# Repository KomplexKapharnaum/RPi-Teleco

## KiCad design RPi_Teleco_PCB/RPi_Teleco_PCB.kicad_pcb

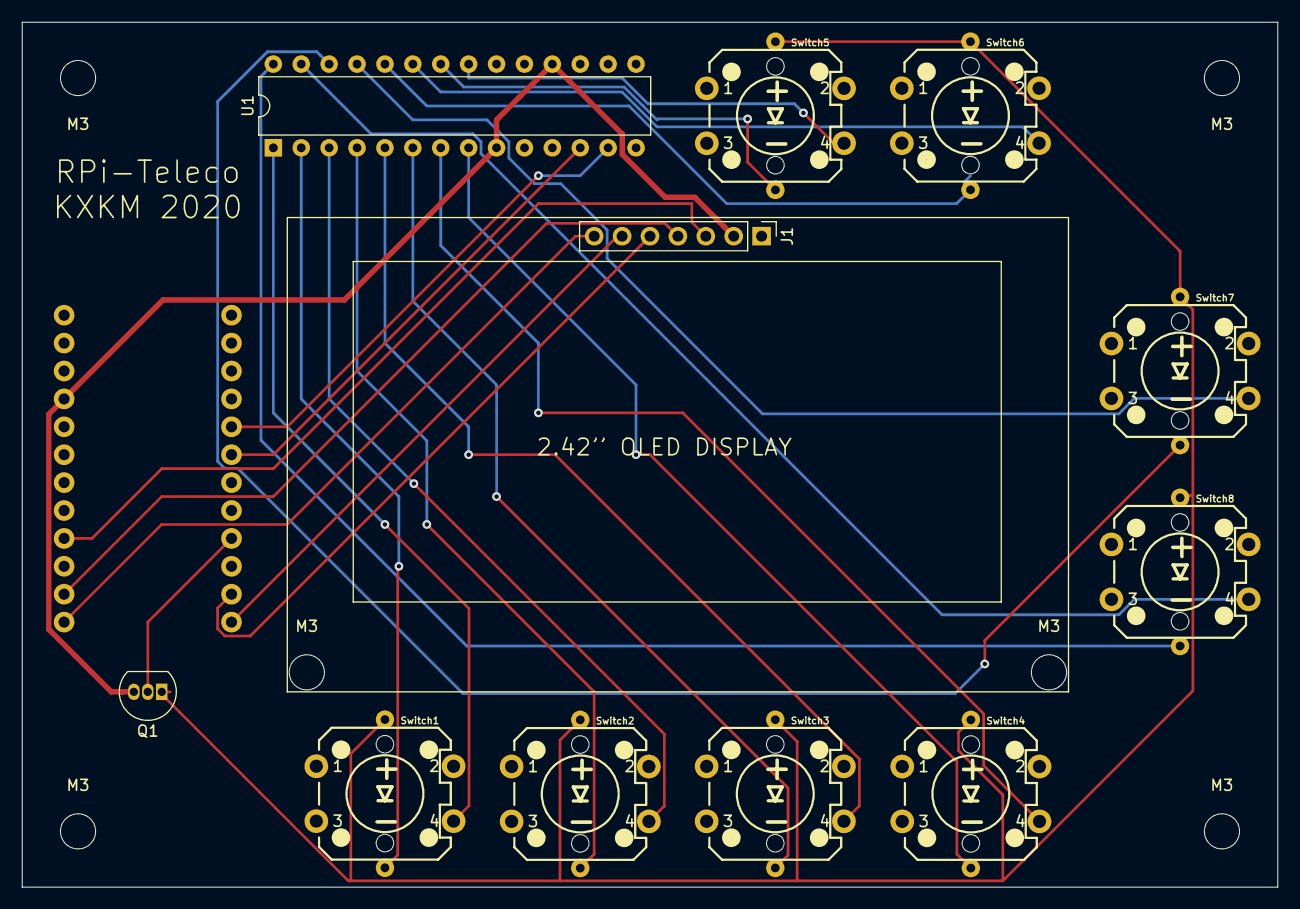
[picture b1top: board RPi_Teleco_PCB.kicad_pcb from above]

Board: 2 copper layers, 114.3 x 78.7 mm, 18 parts (1 on the bottom side), 27 nets.

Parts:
B1: ARDUINO_PRO_MICRO; SPARKFUN_PRO_MICRO
J1: Conn_01x07; PinHeader_1x07_P2.54mm_Vertical
M3, M3#2, M3#3, M3#4, M3#5, M3#6: MountingHole_3.2mm_M3
Q1: PN2222A; TO-92_Inline
Switch1, Switch2, Switch3, Switch4, Switch5, Switch6, Switch7, Switch8: MOMENTARY-SWITCH-SPST-LED-PTH-12MM; TACTILE_SWITCH_LED_PTH_12MM
U1: MCP23017_SP; DIP-28_W7.62mm

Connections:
+5V: B1.21, J1.2, Q1.3, U1.9, U1.18
BTN1: Switch1.4, U1.1
BTN2: Switch2.4, U1.3
BTN3: Switch3.4, U1.5
BTN4: Switch4.4, U1.7
BTN5: Switch5.4, U1.21
BTN6: Switch6.4, U1.23
BTN7: Switch7.4, U1.25
BTN8: Switch8.4, U1.27
CS: B1.13, J1.7
DC: B1.12, J1.6
GND: B1.23, J1.1, Switch1.2, Switch2.2, Switch3.2, Switch4.2, Switch5.2, Switch6.2, Switch7.2, Switch8.2, U1.10, U1.15, U1.16, U1.17
I2C_SCL: B1.6, U1.12
I2C_SDA: B1.5, U1.13
LED1: Switch1.C, U1.2
LED2: Switch2.C, U1.4
LED3: Switch3.C, U1.6
LED4: Switch4.C, U1.8
LED5: Switch5.C, U1.22
LED6: Switch6.C, U1.24
LED7: Switch7.C, U1.26
LED8: Switch8.C, U1.28
Level: Q1.1, Switch1.A, Switch2.A, Switch3.A, Switch4.A, Switch5.A, Switch6.A, Switch7.A, Switch8.A
PWM_LEVEL: B1.9, Q1.2
RES: B1.11, J1.5
SCK: B1.16, J1.3
SDA: B1.14, J1.4

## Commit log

2019-12-11 init
2019-12-12 components
2019-12-12 capture
2020-01-23 draft
2020-01-29 ready
2020-02-03 teleco btn mgmt
2020-02-03 ok case
2020-02-04 casing ok
2020-02-10 case v2
2020-02-11 precautions
2020-02-13 ok input
2020-02-13 teleco ok
2020-02-13 rename btns + up event + hold repeat timing
2020-02-13 hide btns debug
2020-02-14 refresh
2020-03-03 symbols
2020-05-08 GBR Files
2020-06-03 more fonts
2023-03-28 pio version
